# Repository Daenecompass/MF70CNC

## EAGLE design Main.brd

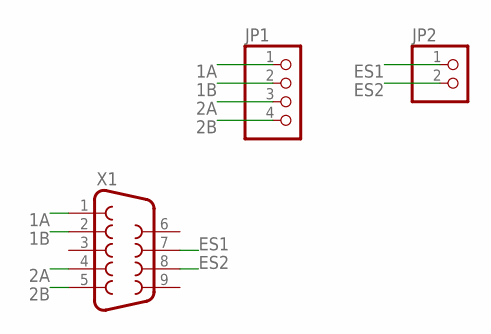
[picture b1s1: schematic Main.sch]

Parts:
JP1: PINHD-1X4; 1X04
JP2: PINHD-1X2; 1X02
X1: F09HP

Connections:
1A: JP1.1, X1.1
1B: JP1.2, X1.2
2A: JP1.3, X1.4
2B: JP1.4, X1.5
ES1: JP2.1, X1.7
ES2: JP2.2, X1.8

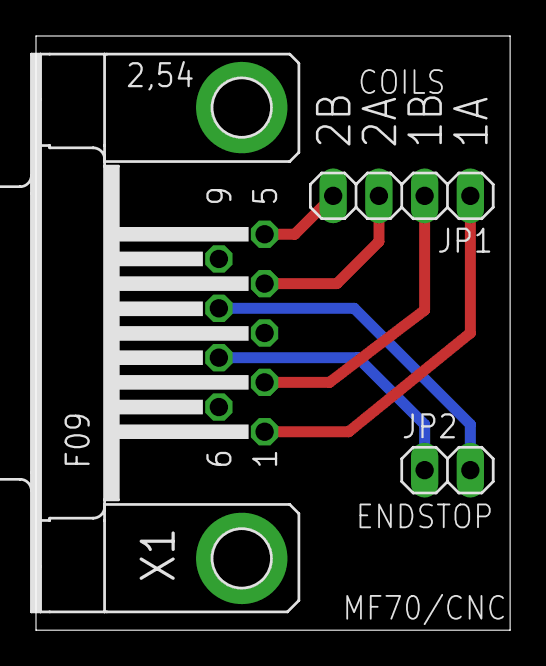
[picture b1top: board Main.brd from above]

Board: 2 copper layers, 26.3 x 33.0 mm, 3 parts (0 on the bottom side), 6 nets.

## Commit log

2016-11-22 First commit.
2016-11-22 Added MF70CNC manual.
